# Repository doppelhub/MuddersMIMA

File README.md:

# MuddersMIMA
 Mudders Take on Manual IMA Control in the G1 Honda Insight

## Firmware directory
### File descriptions
#### Main Ardiuno file
muddersMIMA_firmware.ino

Opening this file in the Arduino IDE will suck in all the other files that the project uses, and present them in separate tabs in the IDE.

It pulls in an h file, ```muddersMIMA.h```, which is discussed below and which draws in all other constant, variable and function definitions.

The main loop calls methods to output status, parse commands, and do work depending on which of three modes is selected by a toggle switch. This is a MITM for MAMODE1, MAMODE2 and CMD_PWR signals from ECM to MCM.

The code is largely self-explanatory if you read the code starting with this ```ino``` file, then the H files as below. Operation is summarized in "How it works", at the end of this page.

#### H Files
```muddersMIMA.h```

This short file pulls in other .H definition files:

```config.h``` - Firmware version and build date.

```cpu_map.h``` - Really a mapping the names of each analog and digital signal to a corresponding pin on the Arduino. It's not really specific to a particular CPU.

```debugLED.h, debugUSB.h``` - functions for turning the LED on and off; functions to display stats. debugUSB provides calls that output status to the user through the serial USB interface. Most interesting: a call to ```ecm_getMAMODE1_state()``` (in ```ecm_signals.h/cpp```) lists the different states the car may be in.

```gpio.h``` - Defines and handles other analog and digital pin inputs and outputs.

```adc.h``` - provides access to joystick inputs.

```USB_userinterface.h``` - parses user's commands and has calls to do the requested work.

```mcm/ecm_signals.h``` - provides accessors for reading ECM commands and sending them to the MCM (these are called from the main loop based on DIP switch position and joystick position.)

## How it works

This is a MITM for three lines: MAMODE1, MAMODE2 and CMDPWR. These come from the ECM and are sent to the MCM. Basically, the current state of each signal is read using accessors in ```ecm_signals.h, cpp``` and the desired state output using functions in ```mcm_signals.h, cpp```.

MAMODE1 in particular communicates desired states using PWM. The signal for each PWM amount is defined in ```ecm_signals.h```. MAMODE2's signals, on or off, are defined there too.

The rest of the code is many small files doing individual things - "gpio" is for buttons and digital signals, "adc" is for the joystick, etc.

The user interface is supported by ```USB_userinterface```'s command parser.

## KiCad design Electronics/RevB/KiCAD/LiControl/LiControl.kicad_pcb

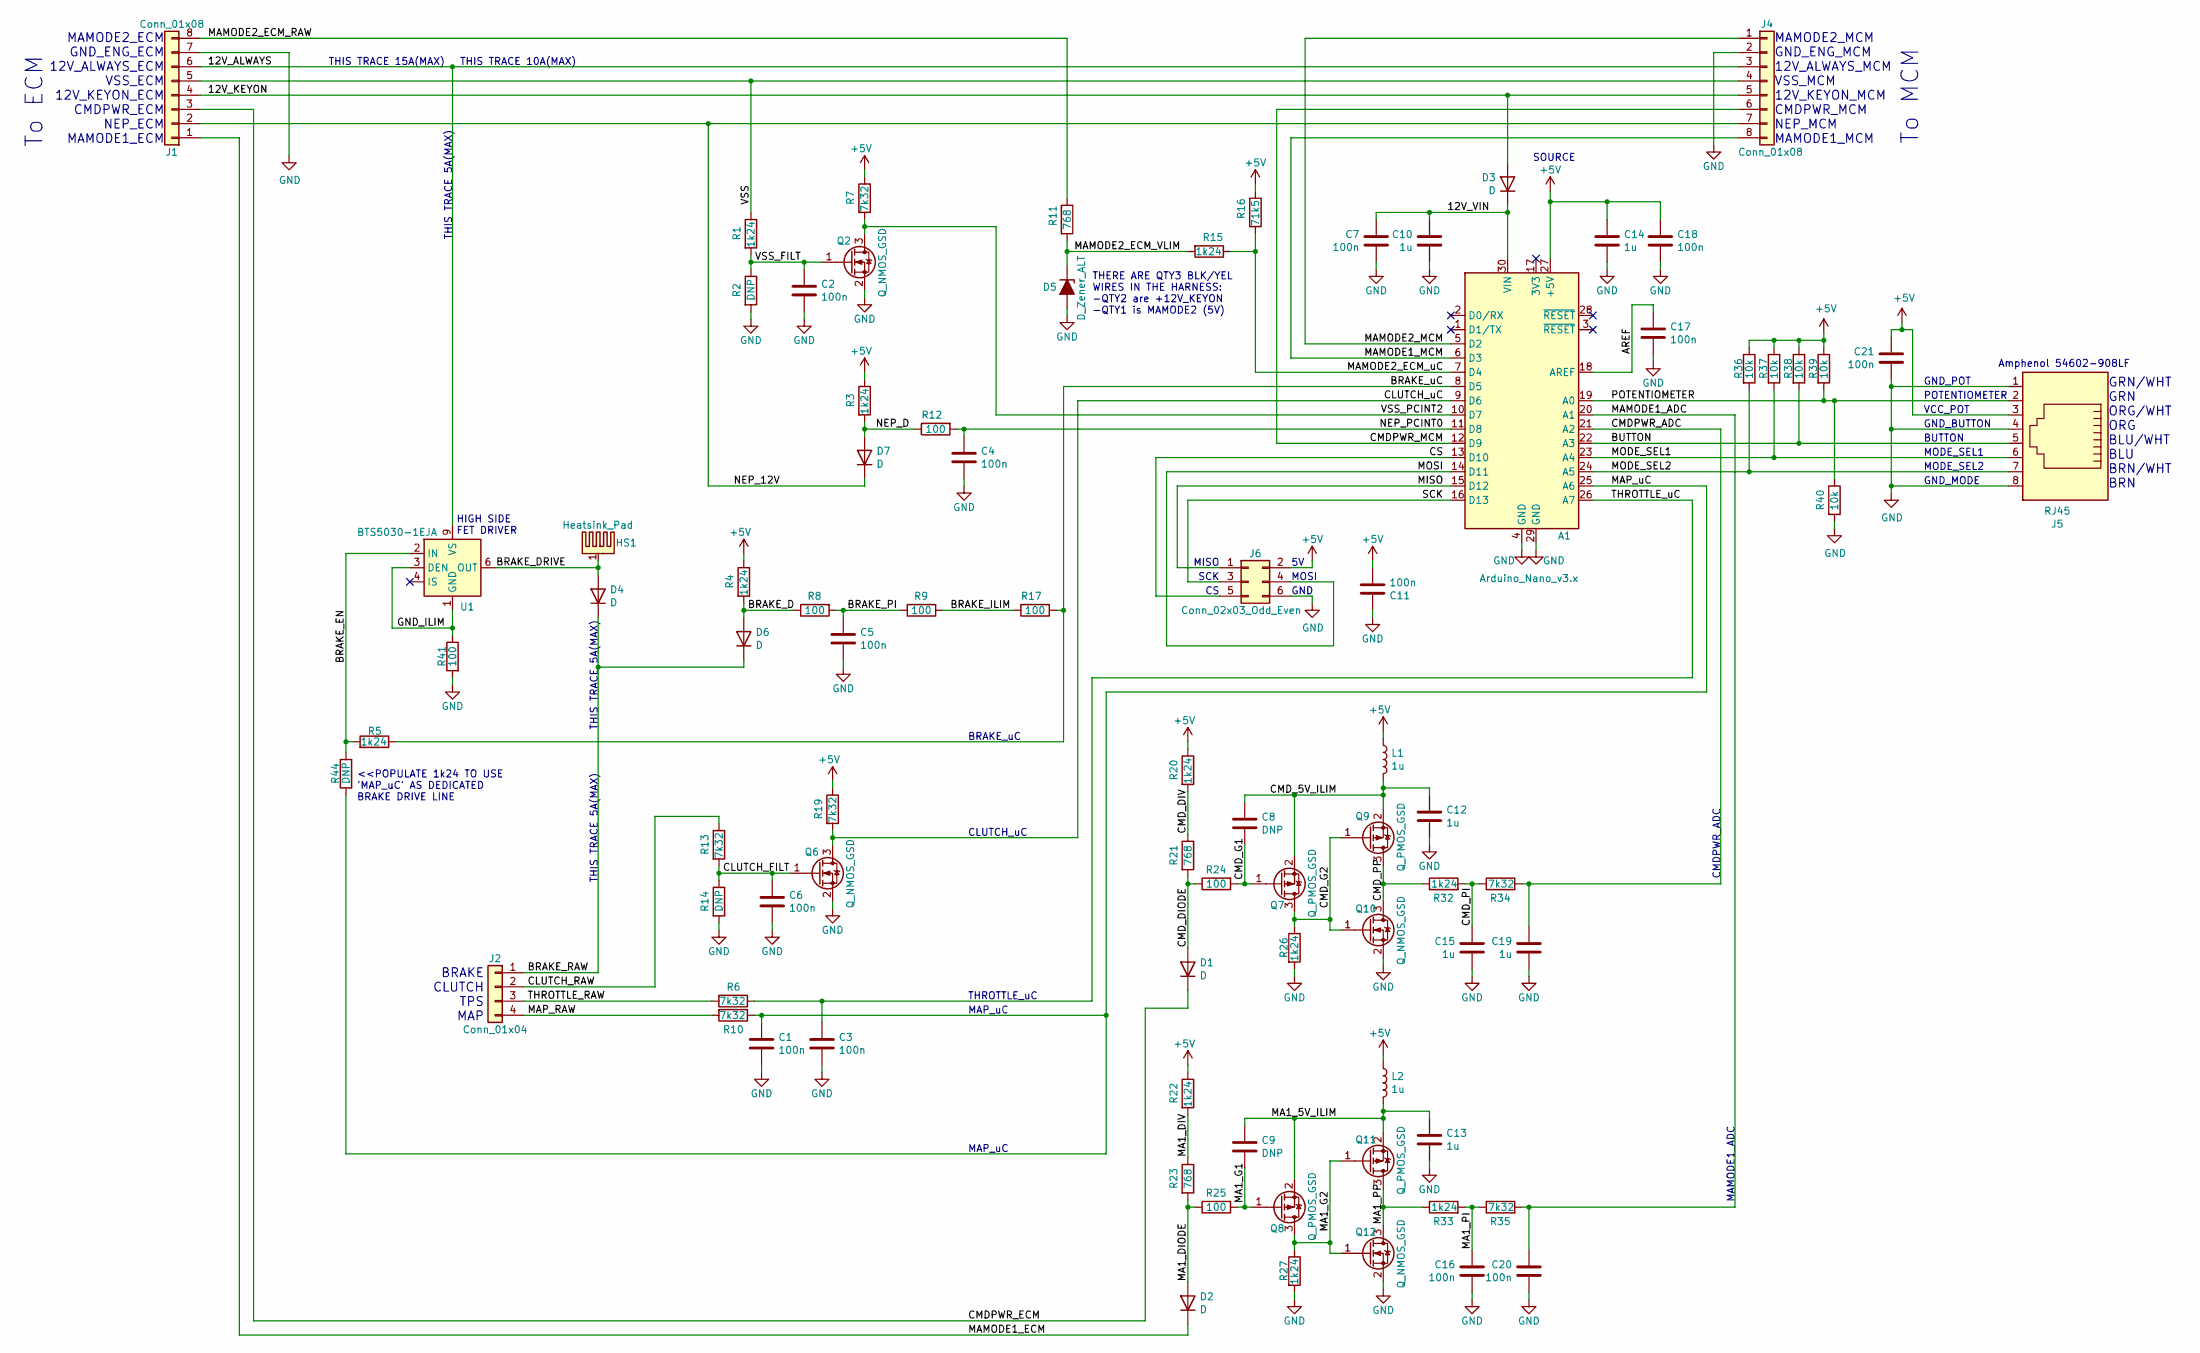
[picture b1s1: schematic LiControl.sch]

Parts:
A1: Arduino_Nano_v3.x; Arduino_Nano
C1, C2, C3, C4, C5, C6, C7, C11, C16, C17, C18, C20, C21: 100n; C_0805_2012Metric
C8, C9: DNP; C_0805_2012Metric
C10, C12, C13, C14, C15, C19: 1u; C_0805_2012Metric
D1, D2, D3, D6, D7: D; D_SOD-123
D4: D; D_SMC
D5: D_Zener_ALT; D_SOD-123
HS1: Heatsink_Pad; Heatsink_AAVID_573300D00010G_TO-263
J1, J4: Conn_01x08; PhoenixContact_MCV_1,5_8-G-3.5_1x08_P3.50mm_Vertical
J2: Conn_01x04; PhoenixContact_MCV_1,5_4-G-3.5_1x04_P3.50mm_Vertical
J5: RJ45; RJ45_Amphenol_54602-x08_Horizontal
J6: Conn_02x03_Odd_Even; PinHeader_2x03_P2.54mm_Vertical
L1, L2: 1u; L_0805_2012Metric
Q2, Q6, Q10, Q12: Q_NMOS_GSD; SOT-23
Q7, Q8, Q9, Q11: Q_PMOS_GSD; SOT-23
R1, R3, R4, R5, R15, R20, R22, R26, R27, R32, R33: 1k24; R_0805_2012Metric
R2, R14, R44: DNP; R_0805_2012Metric
R6, R7, R10, R13, R19, R34, R35: 7k32; R_0805_2012Metric
R8, R9, R12, R17, R24, R25, R41: 100; R_0805_2012Metric
R11, R21, R23: 768; R_0805_2012Metric
R16: 71k5; R_0805_2012Metric
R36, R37, R38, R39, R40: 10k; R_0805_2012Metric
U1: BTS5030-1EJA; Infineon_PG-DSO-8-43

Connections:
+5V: A1.27 (+5V), C11.2, C14.1, C18.1, C21.2, J5.3, J6.2, L1.1, L2.1, R3.1, R4.1, R7.1, R16.1, R19.1, R20.1, R22.1, R36.1, R37.1, R38.1, R39.1
/12V_ALWAYS: J1.6, J4.3, U1.9 (VS)
/12V_KEYON: D3.2 (A), J1.4, J4.5
/12V_VIN: A1.30 (VIN), C7.1, C10.1, D3.1 (K)
/AREF: A1.18 (AREF), C17.1
/BRAKE_D: D6.2 (A), R4.2, R8.1
/BRAKE_DRIVE: D4.2 (A), HS1.1, U1.6 (OUT), U1.7 (OUT), U1.8 (OUT)
/BRAKE_EN: R5.2, R44.1, U1.2 (IN)
/BRAKE_ILIM: R9.2, R17.1
/BRAKE_PI: C5.2, R8.2, R9.1
/BRAKE_RAW: D4.1 (K), D6.1 (K), J2.1
/BRAKE_uC: A1.8 (D5), R5.1, R17.2
/BUTTON: A1.22 (A3), J5.5, R38.2
/CLUTCH_FILT: C6.2, Q6.1 (G), R13.2, R14.1
/CLUTCH_RAW: J2.2, R13.1
/CLUTCH_uC: A1.9 (D6), Q6.3 (D), R19.2
/CMDPWR_ADC: A1.21 (A2), C19.2, R34.2
/CMDPWR_ECM: D1.1 (K), J1.3
/CMDPWR_MCM: A1.12 (D9), J4.6
/CMD_5V_ILIM: C8.2, C12.2, L1.2, Q7.2 (S), Q9.2 (S)
/CMD_DIODE: D1.2 (A), R21.2, R24.1
/CMD_DIV: R20.2, R21.1
/CMD_G1: C8.1, Q7.1 (G), R24.2
/CMD_G2: Q7.3 (D), Q9.1 (G), Q10.1 (G), R26.1
/CMD_PI: C15.2, R32.2, R34.1
/CMD_PP: Q9.3 (D), Q10.3 (D), R32.1
/CS: A1.13 (D10), J6.5
/GND_ILIM: R41.1, U1.1 (GND), U1.3 (DEN)
/MA1_5V_ILIM: C9.2, C13.2, L2.2, Q8.2 (S), Q11.2 (S)
/MA1_DIODE: D2.2 (A), R23.2, R25.1
/MA1_DIV: R22.2, R23.1
/MA1_G1: C9.1, Q8.1 (G), R25.2
/MA1_G2: Q8.3 (D), Q11.1 (G), Q12.1 (G), R27.1
/MA1_PI: C16.2, R33.2, R35.1
/MA1_PP: Q11.3 (D), Q12.3 (D), R33.1
/MAMODE1_ADC: A1.20 (A1), C20.2, R35.2
/MAMODE1_ECM: D2.1 (K), J1.1
/MAMODE1_MCM: A1.6 (D3), J4.8
/MAMODE2_ECM_RAW: J1.8, R11.1
/MAMODE2_ECM_VLIM: D5.1 (K), R11.2, R15.2
/MAMODE2_ECM_uC: A1.7 (D4), R15.1, R16.2
/MAMODE2_MCM: A1.5 (D2), J4.1
/MAP_RAW: J2.4, R10.2
/MAP_uC: A1.25 (A6), C1.2, R10.1, R44.2
/MISO: A1.15 (D12), J6.1
/MODE_SEL1: A1.23 (A4), J5.6, R37.2
/MODE_SEL2: A1.24 (A5), J5.7, R36.2
/MOSI: A1.14 (D11), J6.4
/NEP_12V: D7.1 (K), J1.2, J4.7
/NEP_D: D7.2 (A), R3.2, R12.1
/NEP_PCINT0: A1.11 (D8), C4.2, R12.2
/POTENTIOMETER: A1.19 (A0), J5.2, R39.2, R40.1
/SCK: A1.16 (D13), J6.3
/THROTTLE_RAW: J2.3, R6.2
/THROTTLE_uC: A1.26 (A7), C3.2, R6.1
/VSS: J1.5, J4.4, R1.1
/VSS_FILT: C2.2, Q2.1 (G), R1.2, R2.1
/VSS_PCINT2: A1.10 (D7), Q2.3 (D), R7.2
GND: A1.4 (GND), A1.29 (GND), C1.1, C2.1, C3.1, C4.1, C5.1, C6.1, C7.2, C10.2, C11.1, C12.1, C13.1, C14.2, C15.1, C16.1, C17.2, C18.2, C19.1, C20.1, C21.1, D5.2 (A), J1.7, J4.2, J5.1, J5.4, J5.8, J6.6, Q2.2 (S), Q6.2 (S), Q10.2 (S), Q12.2 (S), R2.2, R14.2, R26.2, R27.2, R40.2, R41.2

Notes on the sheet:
To MCM
SOURCE
GRN/WHT GRN ORG/WHT ORG BLU/WHT BLU BRN/WHT BRN
GND_POT
VCC_POT
GND_MODE
GND_BUTTON
To ECM
THROTTLE_uC
POTENTIOMETER
BUTTON
MODE_SEL1
MODE_SEL2
MAMODE1_ADC
CMDPWR_ADC
Amphenol 54602-908LF
BRAKE CLUTCH TPS MAP
CLUTCH_uC
BRAKE_uC
HIGH SIDE FET DRIVER
THIS TRACE 5A(MAX)
THIS TRACE 15A(MAX)
THIS TRACE 10A(MAX)
MISO
SCK
MOSI
GND
<<POPULATE 1k24 TO USE 'MAP_uC' AS DEDICATED BRAKE DRIVE LINE
MAP_uC
THERE ARE QTY3 BLK/YEL WIRES IN THE HARNESS: -QTY2 are +12V_KEYON -QTY1 is MAMODE2 (5V)
MAMODE2_ECM GND_ENG_ECM 12V_ALWAYS_ECM VSS_ECM 12V_KEYON_ECM CMDPWR_ECM NEP_ECM MAMODE1_ECM
MAMODE2_MCM GND_ENG_MCM 12V_ALWAYS_MCM VSS_MCM 12V_KEYON_MCM CMDPWR_MCM NEP_MCM MAMODE1_MCM

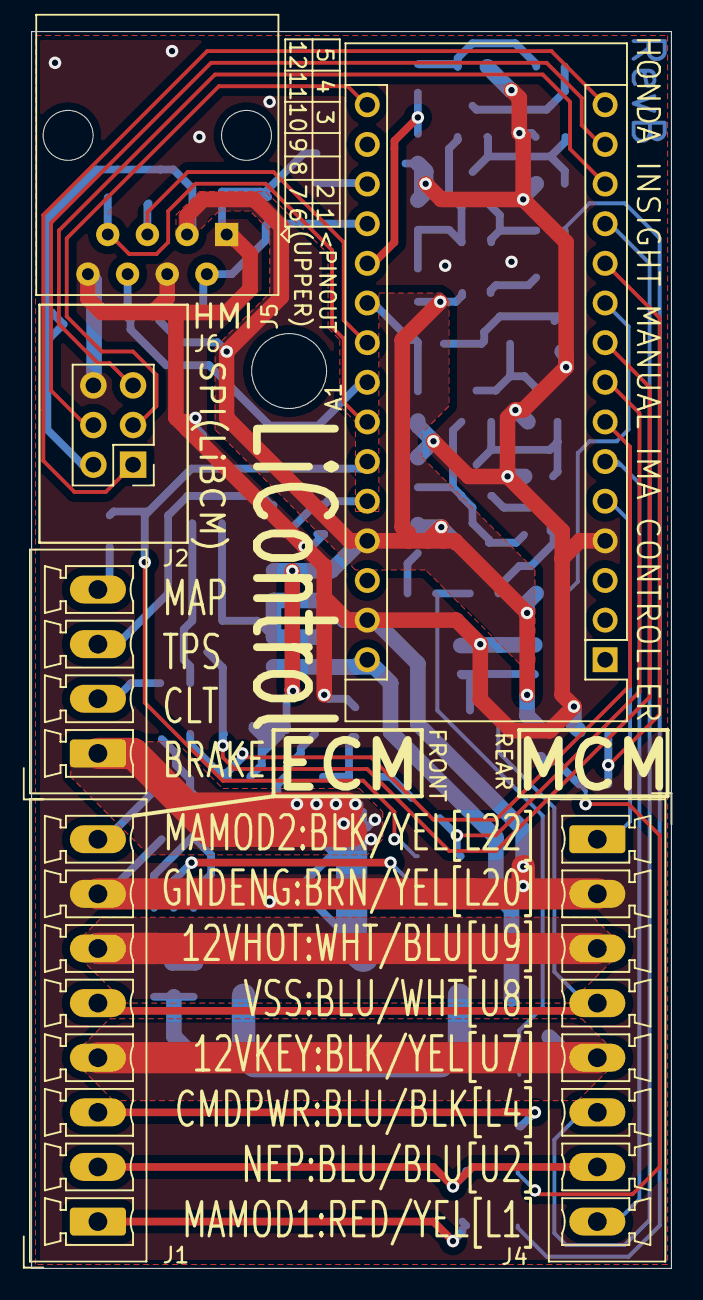
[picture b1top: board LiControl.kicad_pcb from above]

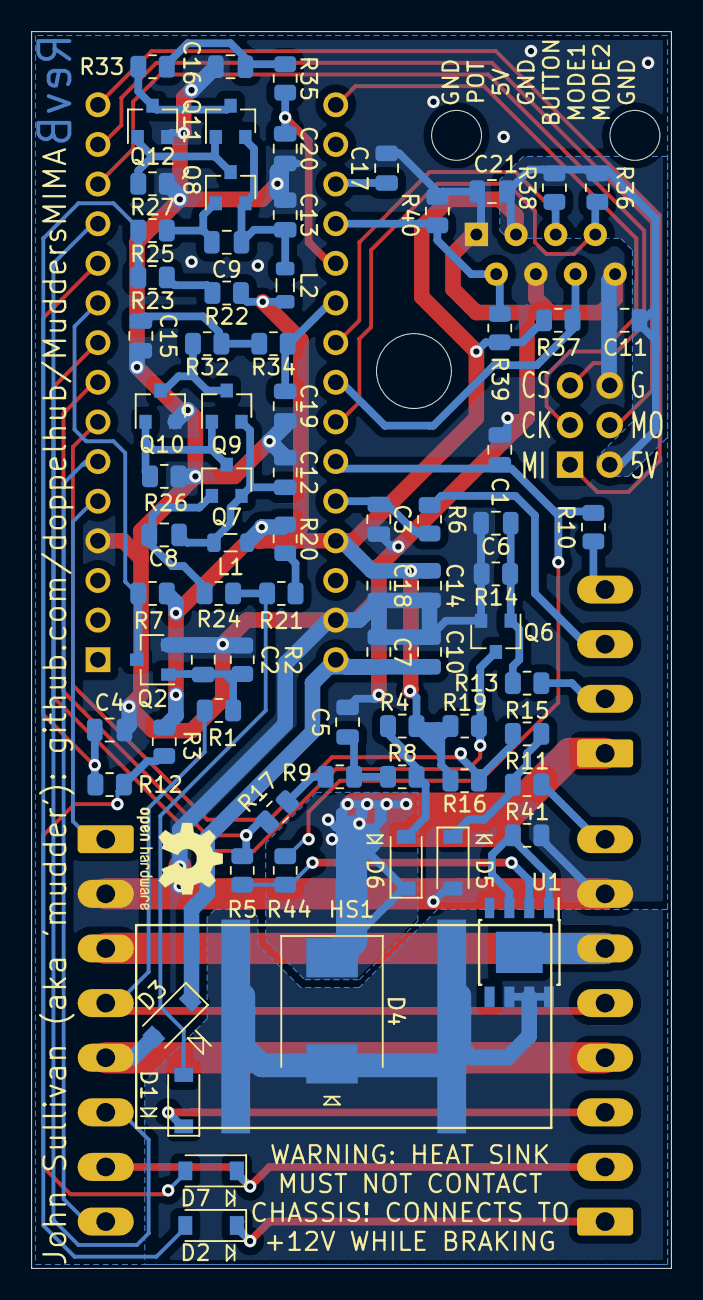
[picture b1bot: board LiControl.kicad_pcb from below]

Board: 2 copper layers, 41.0 x 79.2 mm, 83 parts (77 on the bottom side), 59 nets.

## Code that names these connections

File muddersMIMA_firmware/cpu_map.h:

//Copyright 2022-2023(c) John Sullivan


//cpu_map.h - CPU and pin mapping configuration file
//central pin mapping selection file for different processor types

#ifndef cpu_map_h
#define cpu_map_h

  #ifdef CPU_MAP_ATMEGA328p

      #if defined HW_REVA_REVB
            #define PIN_USER_JOYSTICK  A0
            #define PIN_MAMODE1_ECM    A1
            #define PIN_CMDPWR_ECM     A2
            #define PIN_USER_MOMENTARY A3
            #define PIN_USER_TOGGLE1   A4
            #define PIN_USER_TOGGLE2   A5
            #define PIN_MAP_SENSOR     A6
            #define PIN_THROTTLE       A7

            #define PIN_MAMODE2_MCM     2
            #define PIN_MAMODE1_MCM     3
            #define PIN_MAMODE2_ECM     4
            #define PIN_BRAKE           5
            #define PIN_CLUTCH          6
            #define PIN_VSS             7
            #define PIN_NEP             8
            #define PIN_CMDPWR_MCM      9
            #define PIN_SPI_CS         10
            //#define PIN_SPI_MOSI     11 //default values //already defined
            //#define PIN_SPI_MISO     12
            //#define PIN_SPI_SCK      13

      #endif

  #endif

#endif

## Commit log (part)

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2022-08-09 firmware initial commit
2022-08-10 Added loop message controller
2022-08-10 Added ECM input signals
2022-08-10 OEM signals now pass thru unmodified
    Theoretically this should now pass the OEM signals from the ECM unmodified to the MCM. Next we'll add the 'manual' controls.
2022-08-10 Manual IMA and PHEV Modes Working
2022-08-11 Added schematic
2022-08-11 Added schematic pullups
2022-08-11 Deleted LiBCM log files
2022-08-13 Forked optiboot (unmodified). ReadMe
2022-08-13 Bootloader now bails ASAP unless button pushed down
2022-11-05 Removed powerup beep
2022-11-05 Rewrote Manual IMA mode
    -push button continuous assist/regen added.
    -autostop/start should now work when in manual IMA mode
2023-02-05 RevA Pinout Brainstorming
    Using all 20 I/O pins on MCU
2023-02-06 Future feature notes
2023-02-07 RevA schematic setup
2023-02-09 RevA Schematic Finished, Starting Layout
2023-02-13 Final RevA PCB
2023-05-23 CARs, inverted potentiometer output
2023-05-23 CARs and removed buzzer from firmware
2023-05-23 Fixed 2^10-1 check bug
2023-05-27 LiControl RevB Layout
2023-06-05 RevB PCB
2023-06-06 RevB Bringup Notes
2023-06-15 Added SPI files, updated copyright
2023-06-16 Abstracted all ADC/DAC values to percent
    This might cause jerkiness while driving (100%=100 counts, whereas 8b=256 counts). If so, I'll change everything to '8bPercent' (i.e. 0:255).
2023-06-16 Changed Timer1 to 8b (was 10b)
2023-06-17 Fixed timeout comparison
2023-06-29 Joystick reports % (instead of counts)
2023-07-10 P&P Centroids
2023-07-10 rough brakeLights logic
2023-07-10 P&P changes
2023-07-19 swapped modes, added brake position
2023-08-04 added brake lights during strong regen
2023-08-06 Switch Cutout Template
2023-08-08 Changed Regen Brake Light Enable Value
2023-08-08 Added TPS/MAP/Clutch inputs
2023-08-08 created manual brake light control modes
2023-08-28 no regen brake lights in OEM mode
2023-09-28 engine RPM
2023-10-24 Added HTSUS
2023-12-19 fix: rpm: Count QTY3 ignition pulses per QTY2 revolutions
    We know that the NEP signal read on D8 in `ISR(PCINT0_vect)`
    represents ignition pulse timing: the interrupt is generated when one
    of the ECA1's three cylinders is receiving an ignition pulse.
    Before this commit, we calculated an RPM value by counting each of
    these pulses as a single revolution. This was incorrect, as in our
    four-stroke I3, there are two revolutions per three ignition pulses.
2023-12-19 fix: rpm: Enable pin-change IRQs on port B
    Before this commit, we only adjusted PCMSK0, indicating that among the
    pins on port B, pin 8 alone should be capable of generating pin-change
    interrupts. However, we never actually enabled pin-change interrupts
    on port B at all, making our PCMSK0 setting meaningless.
    Now, enable pin change interrupts on port B by setting the PCIE0 bit
    of the PCICR high.
2023-12-22 feat: speed: Measure vehicle speed using pin-change IRQ on VSS
    This commit implements vehicle speed measurement using a pin-change
    interrupt on the vehicle speed sensor (VSS) line connected to pin D7
    The VSS emits ~4250 pulses per mile[^1] under normal conditions. As
    with NEP, attach a pin-change interrupt; if when the interrupt
    activates, the pin is high, recalculate the vehicle speed by checking
    the time since the last revolution.
2023-12-22 [WIP] feat: Restart from FAS in mode 2
    This is a WIP because this isn't the ideal way to write this code.
    Before this commit, after using regen FAS in mode 2, the ECM will
    spend some time attempting to restart the engine (i.e. switching to
    mode 0 would give us an auto-restart), but eventually give up.
    Now, when the engine is considered "force-stopped", translate the
    momentary button to MAMODE1_STATE_IS_START. Pressing the momentary
2024-01-06 [WIP] feat: mode1: Use live or stored joystick value, whichever is greater
    Before this commit, when in mode 1, a stored assist value was
    overridden by any joystick use. This means that increasing a joystick
    assist value requires us to reduce from stored *down to* manually
    requested value, creating a small jerk as power is instantly changed.
    Now, combine the joystick and stored value if they are in the same
    direction. If a stored value is (absolutely) greater than the current
2024-01-25 [WIP] feat: mode1: Blend in a new map for IMA power based on TPS+VSS+BRAKE
    With this commit, blend a mapped "suggested" CMDPWR value based on the
    vehicle speed and TPS into the actual CMDPWR in LiControl mode 1.
    The mapping is constructed so as to promote the use of IMA power at
    low throttle. This reduces the fatigue of using the IMA joystick,
    essentially allows regen to occur (for driving comfort) as soon as
    driving begins, and (for the CVT specifically) generates a driving
2024-02-14 [WIP] feat: mode1: Blend ECM CMDPWR, too
    UNTESTED CODE
    In response to
    https://www.insightcentral.net/threads/licontrol-support-thread.132434/page-5#post-1538499
    WIP, again.
    UNTESTED CODE
2024-02-20 [WIP] fix: Use OEM control brake light mode whenever OEM CMDPWR used
    Per JTS here: https://www.insightcentral.net/threads/licontrol-support-thread.132434/page-7#post-1538860
    > In short, whenever LiControl passes the ECM CMDPWR signal to the
    > MCM (e.g. Mode0 or this modified Mode1 you speak of), we need to
    > make sure we've configured LiControl to NOT power the brake
    > light. You do this by calling
    > brakeLights_setControlMode(BRAKE_LIGHT_OEM); at the beginning of any
2024-05-30 ECM duty cycle correction
2024-06-03 optimization: Group constants to limit code-size
    As per JTS:
    > The preprocessor will perform all constant-only math if it's all
    grouped together.
    This leaves dynamic memory usage unchanged, but reduces program
    storage space from 7210B to 7146B, and specifically reduces the length
    of this ISR by ~18 bytes[^1].
2024-06-04 User now selects operating modes in config.h
    Also removed one-off prototype hardware #define statements.
2024-06-04 New mode 'PHEV_mudder'
2024-06-05 Remove Mode Switch Debug Description
2024-06-05 CMDPWR LUT & ADC HW Correction
2024-06-05 Allow LiControl to measure OEM brake status
2024-06-05 HW: unlatch brake highside driver
2024-06-05 Renamed Mode1 & Mode2 functions
2024-06-05 version bump
2024-06-06 rename unused operating mode
2024-06-06 joystick position now measured only once per loop
2024-06-13 Update operatingModes.cpp
    add mode_proportional_auto_assist
2024-06-13 Update config.h
    add mode_proportional_auto_assist();
2024-06-14 refined light assist/regen
2024-06-20 Update operatingModes.cpp
    response now linear rather than exponential.
2024-06-21 Update operatingModes.cpp
    defined integers at start of code
2024-06-24 cleanup/optimize: #define magic number; group constants
    Should have dealt with defining magic number in advance. Oops. It's
    fine, though, we can poke this number when someone realizes it's off
    by number%.
    Again, as per JTS, the preprocessor will perform all constant-only
    math if it's all grouped together.
    Grouping the constants together reduces the length fo the ISR by 10
2024-06-26 Comments
2024-06-27 Update operatingModes.h
    add definitions
2025-07-27 BUG notes and comments
2025-08-15 SPI to LiBCM, clutch & over rev logic
    Added SPI connection to LiBCM, clutch lockout, derate under 2100 RPM to 13KW, and over rev protection. Added new blended driving mode.
2025-08-24 Fix assist hold issue: not disengaging when brake peddle pressed.
    Added 200 uS delay in unlatchSignal_BRAKE_uC() after gpio_brakeLights_floatPin().
2025-08-25 Comment changes only
2025-08-26 Simpler implementation of delay fix for assist hold issue
    Revised comments in unlatchSignal_BRAKE_uC() to more fully explain what is going on.
2025-11-25 Add hysterisis to MAP signal
    Adding hysteresis to the MAP signal makes the assist buttery smooth. Without this change it was still possible to trigger P0420 with aggressive throttle inputs at the higher currents when as a result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
2026-01-23 IT WORKS
2026-01-23 cleaning up
2026-01-24 added Utility class and implmented ease_out curve to throttle
2026-01-24 moving to desktop pc
2026-01-24 back to laptop
2026-01-24 added utility_ease_out_cubic_u8 instead of circ and it feels much better
2026-01-25 untested
